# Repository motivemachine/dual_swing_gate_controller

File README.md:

#### Remote linear actuator controller, for a diy open-source gate opener.

Having built a custom driveway gate and hinge setup I found myself shocked at what a quality dual-swing gate opener costs these days. More importantly, they have rather a lack of customization available in how you control or communicate with them, so I've set out to build my own with a pair of 12v linear actuators and a Semtech SX1287 LORA radio module. This is a work in progress.  

I'll be building a custom PCB for the whole thing, but I've tried to design this in such a way that any number of Arduino and related modules would work if hand-wired with jumpers, perfboard, breadboard, etc. Most parts are through-hole, and the ones that are surface mount are large enough hand soldering should be easy. Also makes for easy customization.

##### Current Status
Schematic and first soldered board is complete. Code testing has begun, and has been mostly reliable with a few adjustments needed in error handling functions and long-term robust-ness. 

##### Parts list and design criteria
* **2x 16" stroke linear actuators (12v)** - commercial gate openers are often much larger than this, but so often are the gates larger and heavier. My gates are quite lightweight tubing on ball-bearing hinges, so not much force is needed to open them. The two actuators I have claim a full load current of 3 amps, though I don't expect them to need much more than 1 to open and close these gates
* **2x 8Ah SLA batteries** - the driveway is long enough that trenching AC power out there would be a chore, so I'll be running this off a pair of ~$16 12v batteries and a small solar panel instead.
* **Arduino Pro mini 8Mhz/3.3v** - chosen so that I can avoid level shifting the SPI/I2C modules. An arduino Uno or Nano would work fine with proper level shifting
* **AI-thinker RA-02 Lora** radio - I've come to like these for designs that may be put in varied enclosures, as the IPX connector built-in means I can place the radio anywhere that's convenient and pipe the RF via coax to an optimal antenna placement.
* **4x 12volt SPDT relays** of proper current rating- The relays are in an H-Bridge topology that allows reversing of current through a DC motor(see below). This could be done a little cleaner with a pair of DPDT relays, but using these means the design will also work with the standard 4-place relay modules that are so popular. They are a 12v coil powered off the battery, switched with a PNP from the Atmega328p.
* **2x INA219**- These can be had in SOT23-8 package, or available in several types of breakout boards. These will be the primary safety, which will watch the current going to each actuator. We'll test for a baseline current it usually takes to open a given gate (perhaps in a light breeze) and set that as our upper limit of motor current. If this current is exceeded, it likely means a gate is jammed or attempting to close on an object; so stop and reverse the gate.
  * Most of the pre-built modules I've seen for sale us a 2010 0.1ohm shunt resistor, allowing a maximum current of 3 amps. If your motors draw more than that, recalculate the needed resistor value
  * There will be enough exposed pins to add an electronic-eye, but I haven't planed for that yet.
* **2x mini ATM fuse**- the INA219 will handle over-current due to obstructions in the motor, these are just extra safety in case of a major hardware or wiring failure. Size appropriately to your wire sizes and motor current requirements.
* **AMS1117-3.3 regulator**- For the 3.3v circuitry.
* **A MAG3110 or similar magnetometer**- this is optional, but I've decided to build-in my magnetometer driveway alarm into this same enclosure and power supply. It is described here: [magneto-driveway-alarm](www.gitlab.com/motivemachine/magneto-driveway-alarm)
  * The magnetometer from a more common IMU package (i.e. mpu9250) would likely also work well.

##### H-Bridge description
  
Shown here is the relay configuration in a simple H-Bridge. By switching seperate relays, any leg can be made positive, while the other remains grounded, causing the DC motor to be able to turn in two directions. This is very fault tolerant too- if any relay became stuck or failed, the motor would have either both leads grounded, or both leads at 12 volts, neither one of which would allow current to flow, therefore the motor will remain stopped. If the linear actuator is moving, it will of course stop when it reaches the built-in limit switches.
  Avid home DIY'ers might recognize this as similar to wiring a 3-way light switch, but backwards. The other difference is that AC power has no single direction of current flow, nor does a lightbulb care which way the current flows.

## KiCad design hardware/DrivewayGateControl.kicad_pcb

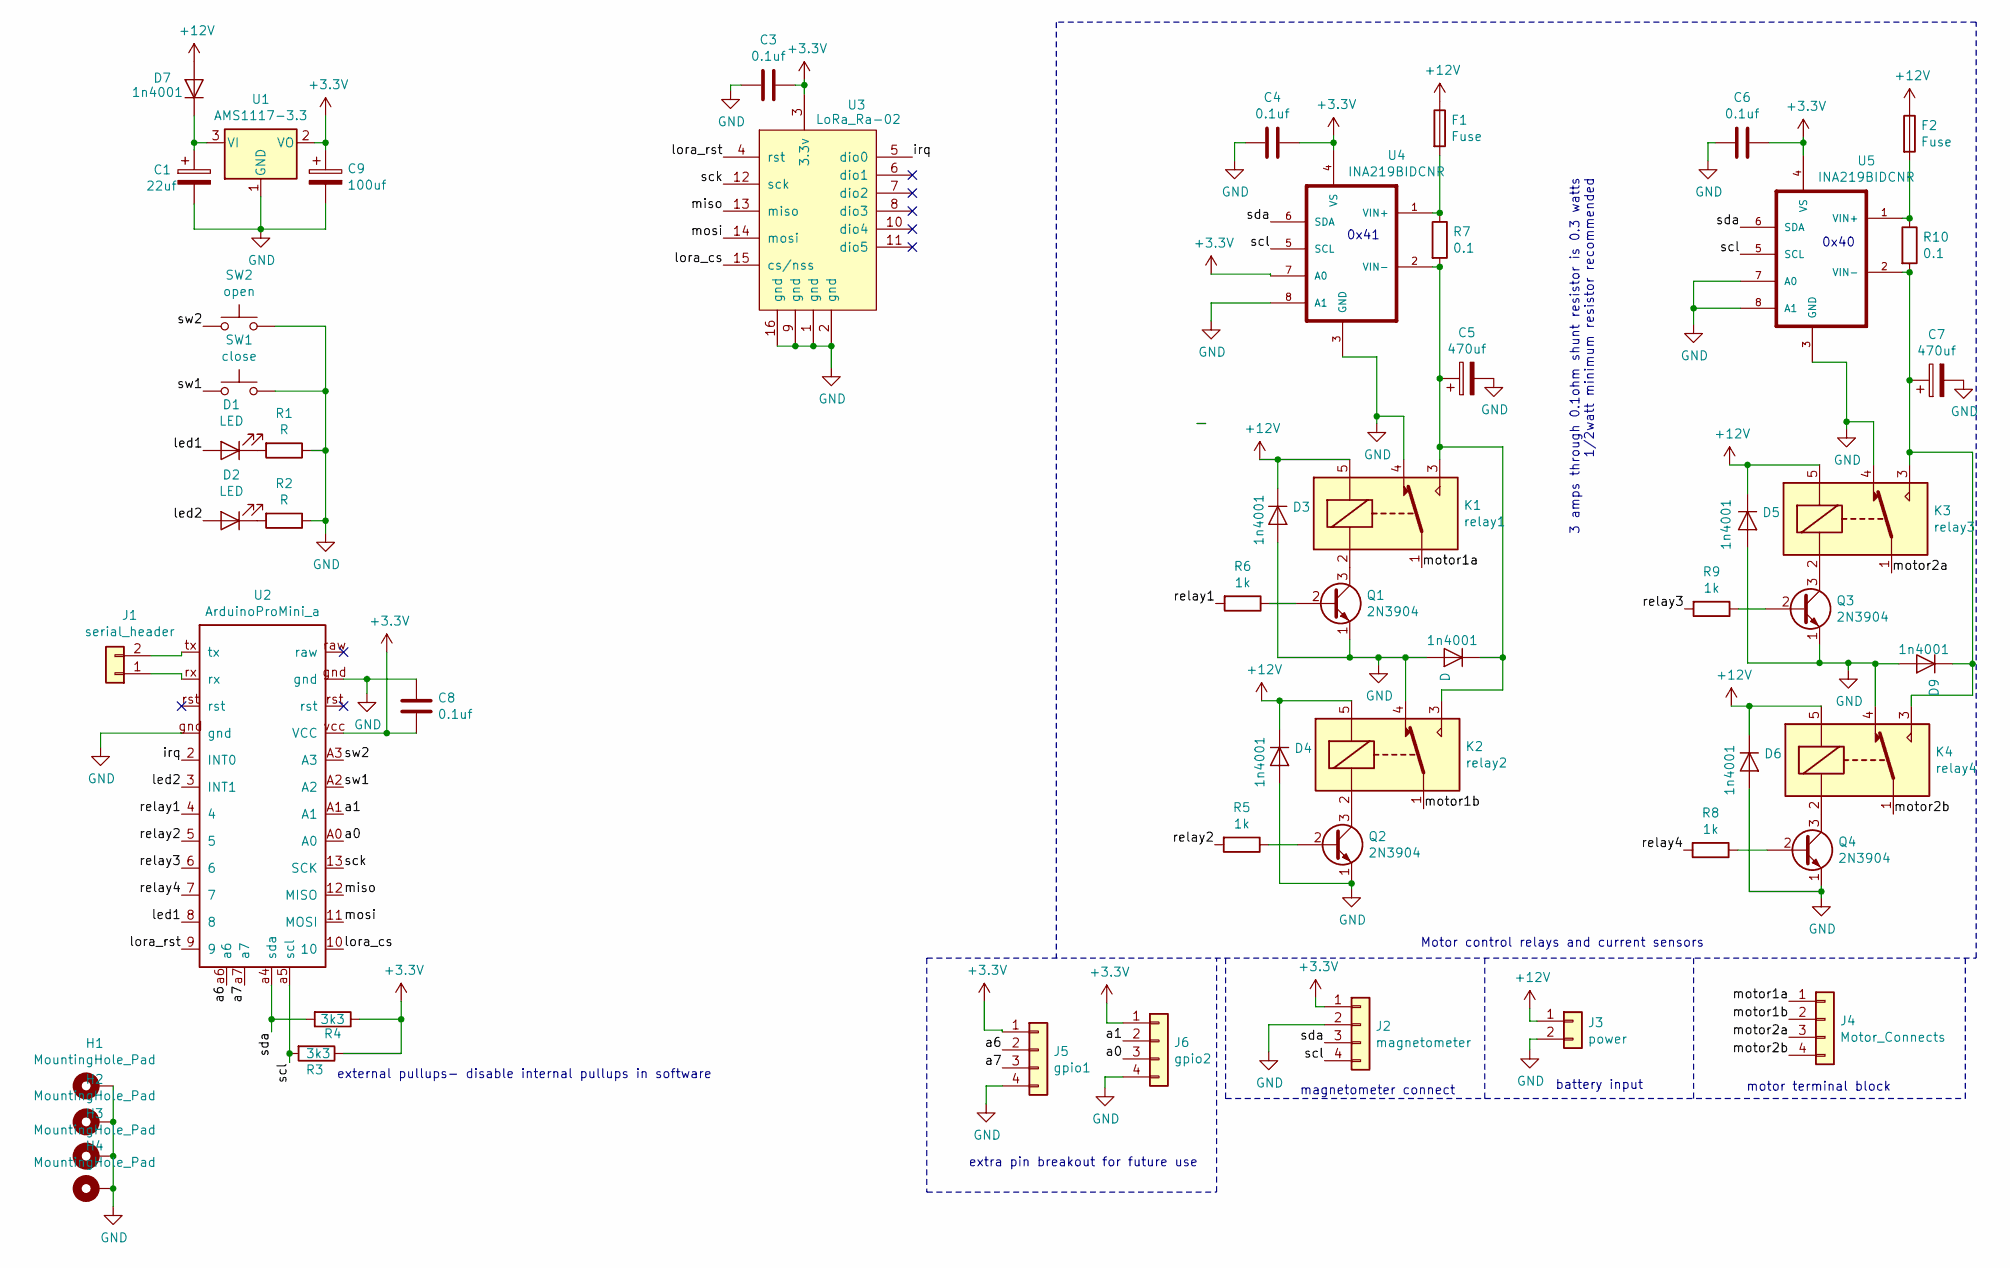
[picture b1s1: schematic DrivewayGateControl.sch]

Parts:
1n4001: D; D_A-405_P7.62mm_Horizontal
C1: 22uf; CP_Radial_D5.0mm_P2.50mm
C3, C4, C6, C8: 0.1uf; C_Disc_D4.7mm_W2.5mm_P5.00mm
C5, C7: 470uf; CP_Radial_D12.5mm_P5.00mm
C9: 100uf; CP_Radial_D7.5mm_P2.50mm
D1, D2: LED; LED_D5.0mm
D3, D4, D5, D6, D7, D9: 1n4001; D_A-405_P7.62mm_Horizontal
F1, F2: Fuse; Fuse_Blade_Mini_directSolder
H1, H2, H3, H4: MountingHole_Pad; MountingHole_3.2mm_M3_Pad_Via
J1: serial_header; PinHeader_1x02_P2.54mm_Vertical
J2: magnetometer; TerminalBlock_bornier-4_P5.08mm
J3: power; TerminalBlock_bornier-2_P5.08mm
J4: Motor_Connects; TerminalBlock_bornier-4_P5.08mm
J5: gpio1; PinHeader_1x04_P2.54mm_Vertical
J6: gpio2; PinHeader_1x04_P2.54mm_Vertical
K1: relay1; Relay_SPDT_SANYOU_SRD_Series_Form_C
K2: relay2; Relay_SPDT_SANYOU_SRD_Series_Form_C
K3: relay3; Relay_SPDT_SANYOU_SRD_Series_Form_C
K4: relay4; Relay_SPDT_SANYOU_SRD_Series_Form_C
Q1, Q2, Q3, Q4: 2N3904; TO-92_Inline_Wide
R1, R2: R; R_Axial_DIN0207_L6.3mm_D2.5mm_P7.62mm_Horizontal
R3, R4: 3k3; R_Axial_DIN0207_L6.3mm_D2.5mm_P7.62mm_Horizontal
R5, R6, R8, R9: 1k; R_Axial_DIN0207_L6.3mm_D2.5mm_P7.62mm_Horizontal
R7, R10: 0.1; R_Axial_DIN0207_L6.3mm_D2.5mm_P10.16mm_Horizontal
SW1: close; SW_PUSH_6mm_H8.5mm
SW2: open; SW_PUSH_6mm_H8.5mm
U1: AMS1117-3.3; SOT-223-3_TabPin2
U2: ArduinoProMini_a
U3: LoRa_Ra-02; LORA_SX1278_Module
U4, U5: INA219BIDCNR; SOT-23-8

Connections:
+3V3: C3.1, C4.1, C6.1, C8.2, C9.1, J2.1, J5.1, J6.1, R3.1, R4.1, U1.2 (VO), U2.vcc (VCC), U3.3 (3.3v), U4.4 (VS), U4.7 (A0), U5.4 (VS)
+12V: D3.1 (K), D4.1 (K), D5.1 (K), D6.1 (K), D7.2 (A), F1.1, F2.1, J3.1, K1.5, K2.5, K3.5, K4.5
/a0: J6.3, U2.A0
/a1: J6.2, U2.A1
/a6: J5.2, U2.a6
/a7: J5.3, U2.a7
/irq: U2.2 (INT0), U3.5 (dio0)
/led1: D1.2 (A), U2.8
/led2: D2.2 (A), U2.3 (INT1)
/lora_cs: U2.10, U3.15 (cs/nss)
/lora_rst: U2.9, U3.4 (rst)
/miso: U2.12 (MISO), U3.13 (miso)
/mosi: U2.11 (MOSI), U3.14 (mosi)
/motor1a: J4.1, K1.1
/motor1b: J4.2, K2.1
/motor2a: J4.3, K3.1
/motor2b: J4.4, K4.1
/relay1: R6.2, U2.4
/relay2: R5.2, U2.5
/relay3: R9.2, U2.6
/relay4: R8.2, U2.7
/sck: U2.13 (SCK), U3.12 (sck)
/scl: J2.4, R3.2, U2.a5 (scl), U4.5 (SCL), U5.5 (SCL)
/sda: J2.3, R4.2, U2.a4 (sda), U4.6 (SDA), U5.6 (SDA)
/sw1: SW1.1, U2.A2
/sw2: SW2.1, U2.A3
GND: 1n4001.2 (A), C1.2, C3.2, C4.2, C5.2, C6.2, C7.2, C8.1, C9.2, D3.2 (A), D4.2 (A), D5.2 (A), D6.2 (A), D9.2 (A), H1.1, H2.1, H3.1, H4.1, J2.2, J3.2, J5.4, J6.4, K1.4, K2.4, K3.4, K4.4, Q1.1 (E), Q2.1 (E), Q3.1 (E), Q4.1 (E), R1.1, R2.1, SW1.2, SW2.2, U1.1 (GND), U2.gnd, U3.1 (gnd), U3.2 (gnd), U3.9 (gnd), U3.16 (gnd), U4.3 (GND), U4.8 (A1), U5.3 (GND), U5.7 (A0), U5.8 (A1)
unnamed: 1n4001.1 (K), C5.1, K1.3, K2.3, R7.2, U4.2 (VIN-)
unnamed: C1.1, D7.1 (K), U1.3 (VI)
unnamed: C7.1, D9.1 (K), K3.3, K4.3, R10.2, U5.2 (VIN-)
unnamed: D1.1 (K), R1.2
unnamed: D2.1 (K), R2.2
unnamed: F1.2, R7.1, U4.1 (VIN+)
unnamed: F2.2, R10.1, U5.1 (VIN+)
unnamed: J1.1, U2.rx
unnamed: J1.2, U2.tx
unnamed: K1.2, Q1.3 (C)
unnamed: K2.2, Q2.3 (C)
unnamed: K3.2, Q3.3 (C)
unnamed: K4.2, Q4.3 (C)
unnamed: Q1.2 (B), R6.1
unnamed: Q2.2 (B), R5.1
unnamed: Q3.2 (B), R9.1
unnamed: Q4.2 (B), R8.1

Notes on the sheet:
Motor control relays and current sensors
motor terminal block
battery input
magnetometer connect
0x41
0x40
external pullups- disable internal pullups in software
extra pin breakout for future use
3 amps through 0.1ohm shunt resistor is 0.3 watts 1/2watt minimum resistor recommended

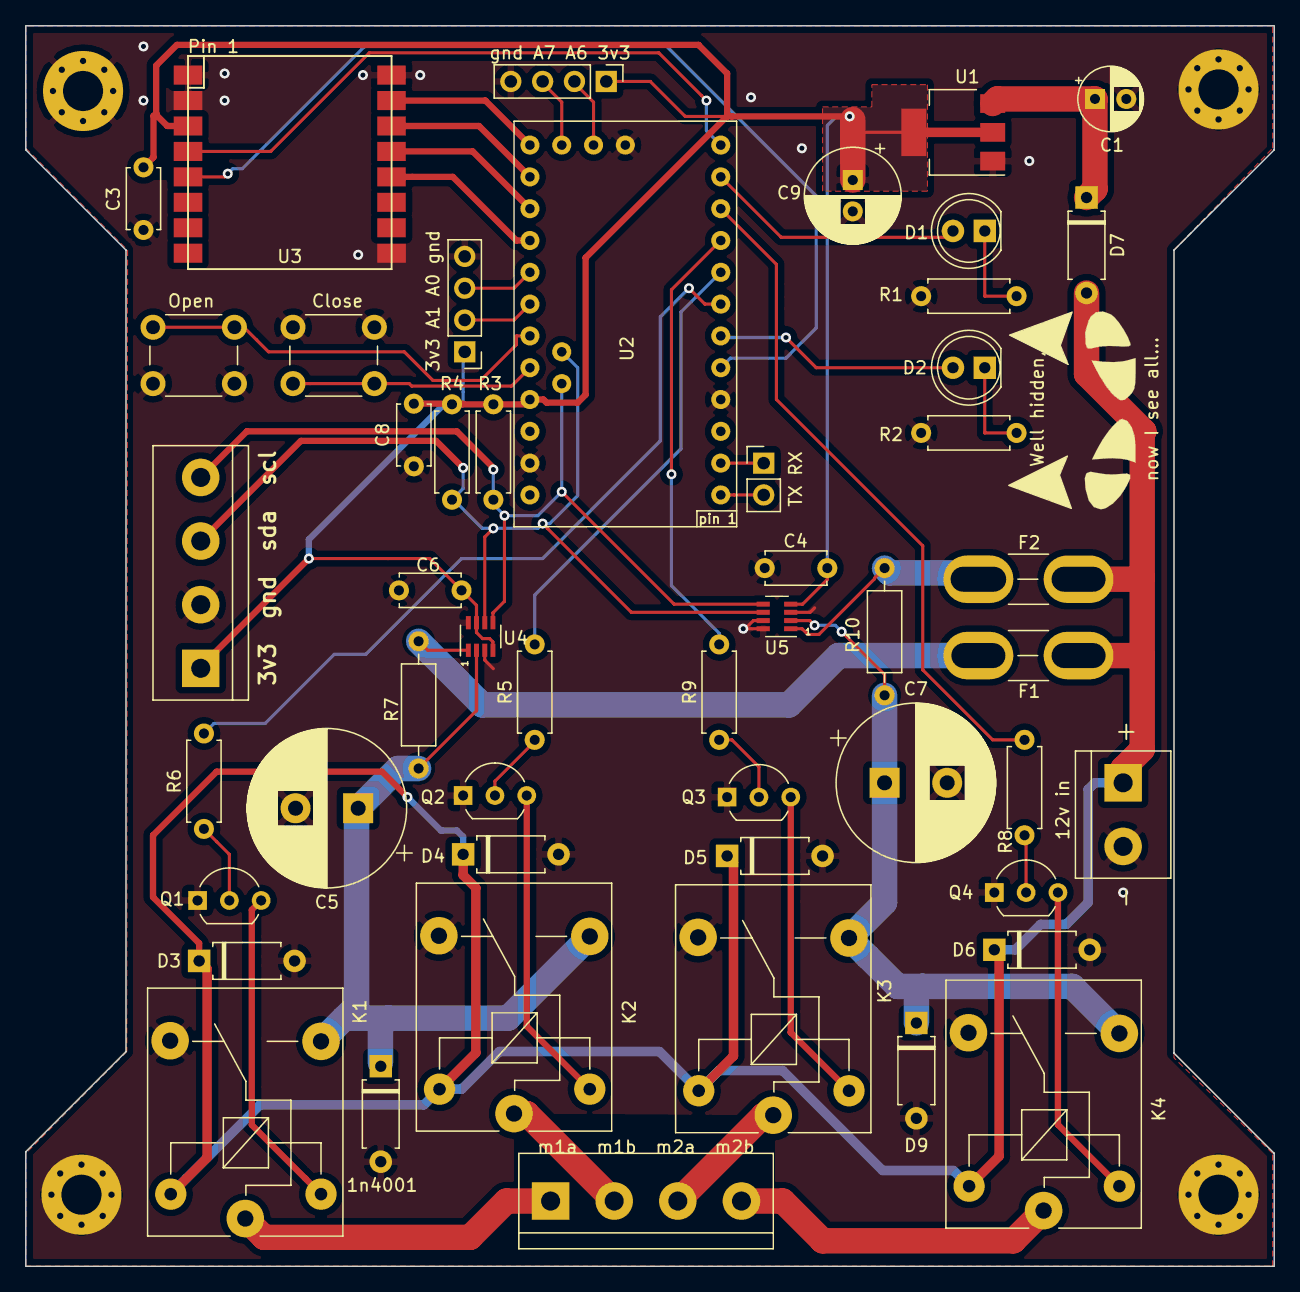
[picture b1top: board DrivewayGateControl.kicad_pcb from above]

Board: 2 copper layers, 99.7 x 99.1 mm, 54 parts (0 on the bottom side), 44 nets.

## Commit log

2019-07-03 upload design files
2019-07-03 Add LICENSE
2019-07-03 housekeeping
2019-07-06 fixed wildly wrong shunt resistor value
2019-07-09 software upload
2019-07-30 update silkscreen, add more pin breakouts
2019-07-30 moving files
2019-07-30 fix typos
2019-09-04 added new fault detections
2019-09-07 fixed relay switch issue
2019-10-04 fix serial glitch and adjust error functions
2019-12-18 tweaked current limits
